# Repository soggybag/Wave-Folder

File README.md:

# Wave Folder (Eurorack 4HP)

YuSynth wavefolder reworked as a 4HP Eurorack module: BAV99 pairs, matched NPN VCA, split boards. KiCad project in `Wave_Folder/`, panel in `Front-Panel/`.

**Status:** PCB and fab files done; not ordered. YuSynth designs are shared for DIY use: ask before selling.

Product notes and ratings: `../Product Notes.md`, `../Project Status.xlsx`.

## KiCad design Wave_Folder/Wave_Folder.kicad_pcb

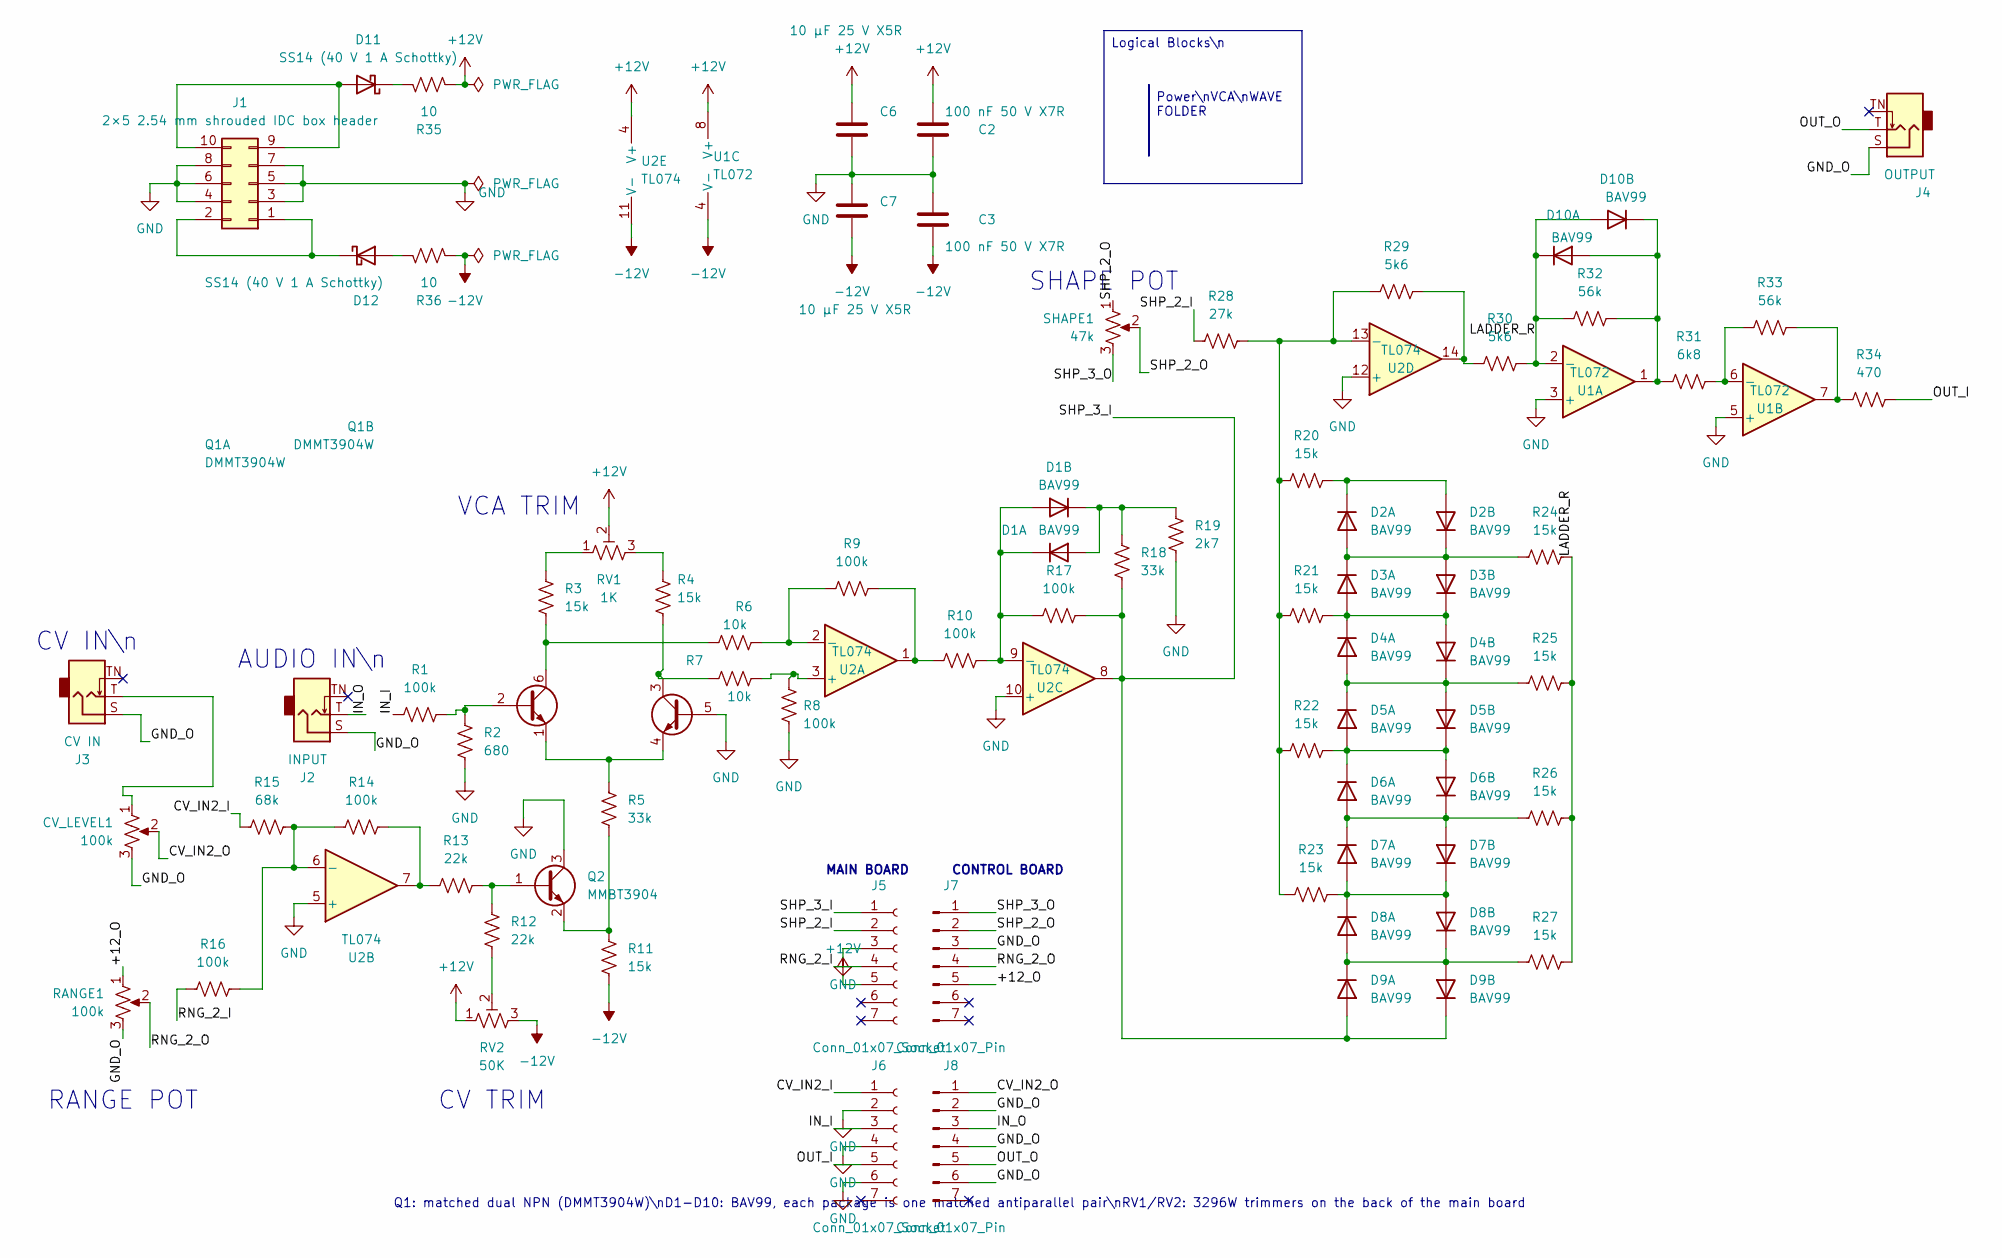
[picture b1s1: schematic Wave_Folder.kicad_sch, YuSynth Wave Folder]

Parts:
C2, C3: 100 nF 50 V X7R; C_0805_2012Metric; LCSC C49678
C6, C7: 10 µF 25 V X5R; C_0805_2012Metric; LCSC C15850
CV_LEVEL1: 100k; Potentiometer_Alpha_RD901F-40-00D_Single_Vertical
D1, D2, D3, D4, D5, D6, D7, D8, D9, D10: BAV99; SOT-23; LCSC C2500
D11, D12: SS14 (40 V 1 A Schottky); D_SMA; LCSC C2480
J1: 2×5 2.54 mm shrouded IDC box header; IDC-Header_2x05_P2.54mm_Vertical
J2: INPUT; Jack_3.5mm_QingPu_WQP-PJ398SM_Vertical_CircularHoles
J3: CV IN; Jack_3.5mm_QingPu_WQP-PJ398SM_Vertical_CircularHoles
J4: OUTPUT; Jack_3.5mm_QingPu_WQP-PJ398SM_Vertical_CircularHoles
J5, J6: Conn_01x07_Socket; PinSocket_1x07_P2.54mm_Vertical
J7, J8: Conn_01x07_Pin; PinHeader_1x07_P2.54mm_Vertical
Q1: DMMT3904W; SOT-363_SC-70-6; LCSC C155305
Q2: MMBT3904; SOT-23; LCSC C20526
R1, R8, R9, R10, R14, R16, R17: 100k; R_0805_2012Metric; LCSC C149504
R2: 680; R_0805_2012Metric; LCSC C17798
R3, R4, R11, R20, R21, R22, R23, R24, R25, R26, R27: 15k; R_0805_2012Metric; LCSC C17475
R5, R18: 33k; R_0805_2012Metric; LCSC C17633
R6, R7: 10k; R_0805_2012Metric; LCSC C17414
R12, R13: 22k; R_0805_2012Metric; LCSC C17560
R15: 68k; R_0805_2012Metric; LCSC C17801
R19: 2k7; R_0805_2012Metric; LCSC C17530
R28: 27k; R_0805_2012Metric; LCSC C17593
R29, R30: 5k6; R_0805_2012Metric; LCSC C4382
R31: 6k8; R_0805_2012Metric; LCSC C17772
R32, R33: 56k; R_0805_2012Metric; LCSC C17756
R34: 470; R_0805_2012Metric; LCSC C17710
R35, R36: 10; R_0805_2012Metric; LCSC C17415
RANGE1: 100k; Potentiometer_Alpha_RD901F-40-00D_Single_Vertical
RV1: 1K; Potentiometer_Bourns_3296W_Vertical
RV2: 50K; Potentiometer_Bourns_3296W_Vertical
SHAPE1: 47k; Potentiometer_Alpha_RD901F-40-00D_Single_Vertical
U1: TL072; SOIC-8_3.9x4.9mm_P1.27mm; LCSC C6961
U2: TL074; SOIC-14_3.9x8.7mm_P1.27mm; LCSC C6963

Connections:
+12V: C2.1, C6.1, J5.5, R35.1, RV1.2, RV2.1, U1.8 (V+), U2.4 (V+)
-12V: C3.2, C7.2, R11.2, R36.1, RV2.3, U1.4 (V-), U2.11 (V-)
/+12_O: J7.5, RANGE1.1
/CV_IN2_I: J6.1, R15.1
/CV_IN2_O: CV_LEVEL1.2, J8.1
/GND_O: CV_LEVEL1.3, J2.S, J3.S, J4.S, J7.3, J8.2, J8.4, J8.6, RANGE1.3
/IN_I: J6.3, R1.1
/IN_O: J2.T, J8.3
/LADDER_R: D10.3 (K), R24.2, R25.2, R26.2, R27.2, R30.2, R32.1, U1.2 (-)
/OUT_I: J6.5, R34.2
/OUT_O: J4.T, J8.5
/RNG_2_I: J5.4, R16.1
/RNG_2_O: J7.4, RANGE1.2
/SHP_2_I: J5.2, R28.1
/SHP_2_O: J7.2, SHAPE1.1, SHAPE1.2
/SHP_3_I: D9.1 (A), D9.2 (K), J5.1, R17.2, R18.2, U2.8
/SHP_3_O: J7.1, SHAPE1.3
GND: C2.2, C3.1, C6.2, C7.1, J1.3, J1.4, J1.5, J1.6, J1.7, J1.8, J5.3, J6.2, J6.4, J6.6, Q1.5 (B2), Q2.3 (C), R2.2, R8.2, R19.2, U1.3 (+), U1.5 (+), U2.5 (+), U2.10 (+), U2.12 (+)
unnamed: CV_LEVEL1.1, J3.T
unnamed: D1.1 (A), D1.2 (K), R18.1, R19.1
unnamed: D1.3 (K), R10.2, R17.1, U2.9 (-)
unnamed: D2.1 (A), D2.2 (K), D3.3 (K), R24.1
unnamed: D2.3 (K), R20.2
unnamed: D3.1 (A), D3.2 (K), D4.3 (K), R21.2
unnamed: D4.1 (A), D4.2 (K), D5.3 (K), R25.1
unnamed: D5.1 (A), D5.2 (K), D6.3 (K), R22.2
unnamed: D6.1 (A), D6.2 (K), D7.3 (K), R26.1
unnamed: D7.1 (A), D7.2 (K), D8.3 (K), R23.2
unnamed: D8.1 (A), D8.2 (K), D9.3 (K), R27.1
unnamed: D10.1 (A), D10.2 (K), R31.1, R32.2, U1.1
unnamed: D11.2 (A), J1.9, J1.10
unnamed: D11.1 (K), R35.2
unnamed: D12.2 (A), R36.2
unnamed: D12.1 (K), J1.1, J1.2
unnamed: Q1.2 (B1), R1.2, R2.1
unnamed: Q1.6 (C1), R3.2, R6.1
unnamed: Q1.1 (E1), Q1.4 (E2), R5.1
unnamed: Q1.3 (C2), R4.2, R7.1
unnamed: Q2.1 (B), R12.1, R13.2
unnamed: Q2.2 (E), R5.2, R11.1
unnamed: R3.1, RV1.1
unnamed: R4.1, RV1.3
unnamed: R9.2, R10.1, U2.1
unnamed: R12.2, RV2.2
unnamed: R13.1, R14.2, U2.7
unnamed: R29.2, R30.1, U2.14
unnamed: R33.2, R34.1, U1.7
unnamed: R31.2, R33.1, U1.6 (-)
unnamed: R7.2, R8.1, U2.3 (+)
unnamed: R6.2, R9.1, U2.2 (-)
unnamed: R14.1, R15.2, R16.2, U2.6 (-)
unnamed: R20.1, R21.1, R22.1, R23.1, R28.2, R29.1, U2.13 (-)

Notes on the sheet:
AUDIO IN\n
VCA TRIM
CV IN\n
RANGE POT
SHAPE POT
CV TRIM
Power\nVCA\nWAVE FOLDER
Logical Blocks\n
MAIN BOARD
CONTROL BOARD
Q1: matched dual NPN (DMMT3904W)\nD1-D10: BAV99, each package is one matched antiparallel pair\nRV1/RV2: 3296W trimmers on the back of the main board

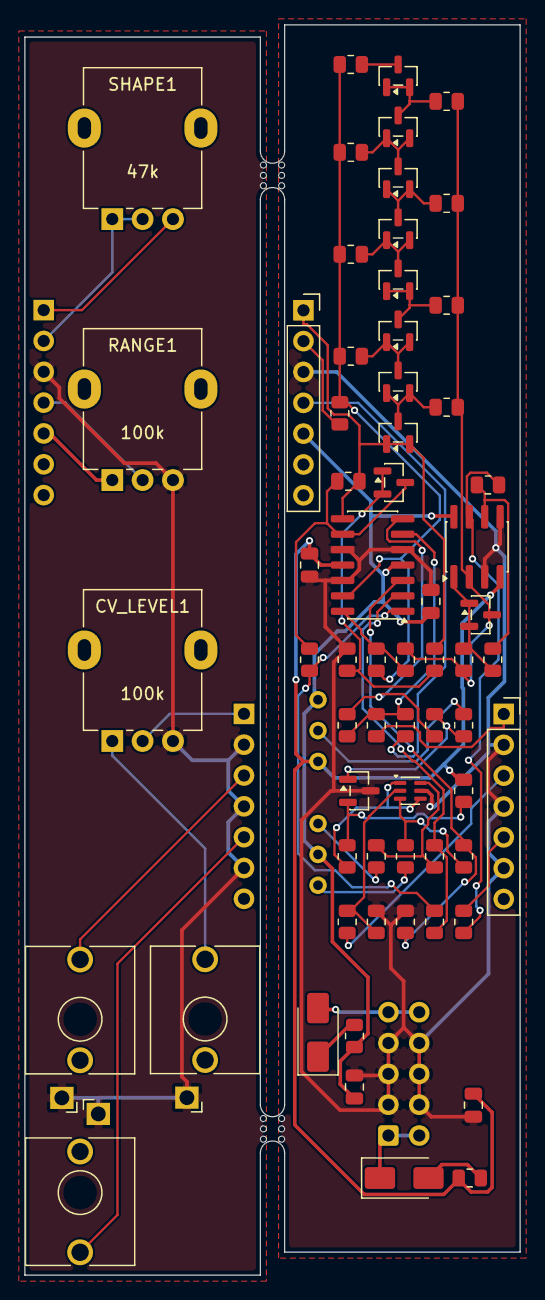
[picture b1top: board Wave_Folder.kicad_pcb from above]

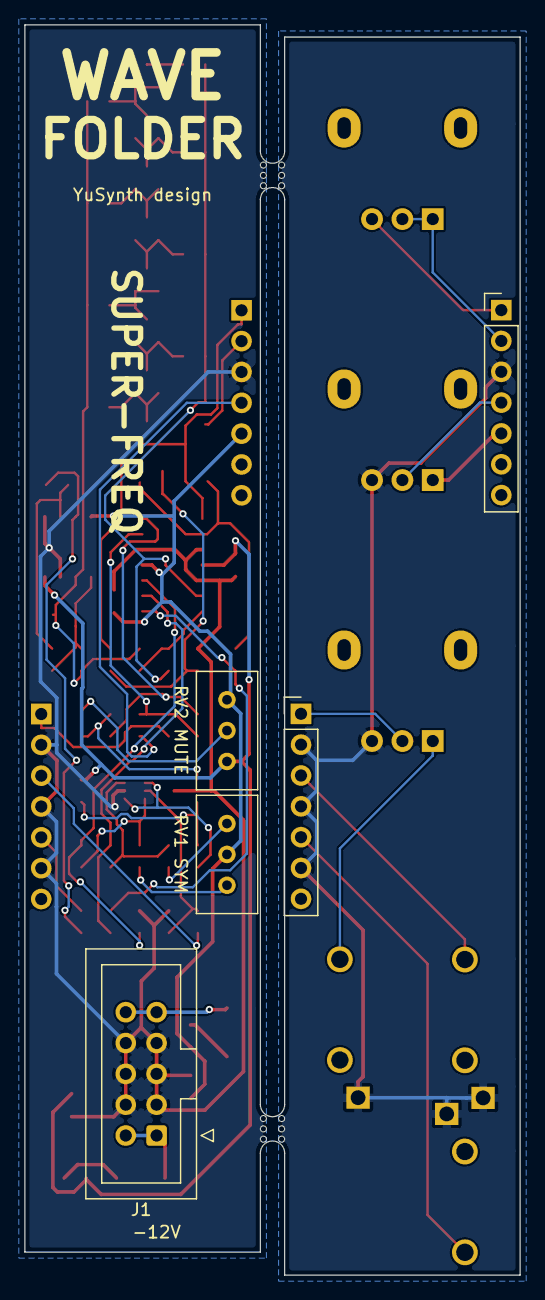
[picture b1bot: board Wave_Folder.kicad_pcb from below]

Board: 2 copper layers, 40.8 x 103.0 mm, 69 parts (5 on the bottom side), 52 nets.

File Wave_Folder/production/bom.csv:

Designator,Footprint,Quantity,Value,LCSC Part #
"C2, C3",0805,2,100 nF 50 V X7R,C49678
"C6, C7",0805,2,10 µF 25 V X5R,C15850
"D1, D10, D2, D3, D4, D5, D6, D7, D8, D9",SOT-23,10,BAV99,C2500
"D11, D12",D_SMA,2,SS14 (40 V 1 A Schottky),C2480
Q1,SOT-363_SC-70-6,1,DMMT3904W,C155305
Q2,SOT-23,1,MMBT3904,C20526
"R1, R10, R14, R16, R17, R8, R9",0805,7,100k,C149504
"R11, R20, R21, R22, R23, R24, R25, R26, R27, R3, R4",0805,11,15k,C17475
"R12, R13",0805,2,22k,C17560
R15,0805,1,68k,C17801
"R18, R5",0805,2,33k,C17633
R19,0805,1,2k7,C17530
R2,0805,1,680,C17798
R28,0805,1,27k,C17593
"R29, R30",0805,2,5k6,C4382
R31,0805,1,6k8,C17772
"R32, R33",0805,2,56k,C17756
R34,0805,1,470,C17710
"R35, R36",0805,2,10,C17415
"R6, R7",0805,2,10k,C17414
U1,SOIC-8_3.9x4.9mm_P1.27mm,1,TL072,C6961
U2,SOIC-14_3.9x8.7mm_P1.27mm,1,TL074,C6963
